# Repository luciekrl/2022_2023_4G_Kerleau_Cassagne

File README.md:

# 2022_2023_4G_Kerleau_Cassagne
Projet Capteur 4GP

## 1. Présentation du projet
### 1.1 Cadre du projet 

Ce projet de réalisation d’un capteur se basant sur une technologie low tech nous a été proposé dans le cadre du cours intitulé “du capteur au banc de test en open source hardware” que nous avons suivi lors de notre 2ème année de cycle ingénieur à l’INSA Toulouse au sein du département Génie Physique. 

Afin de récupérer les données de déformation à partir du capteur, nous avons utilisé une carte Arduino UNO. L’affichage des données se fait d’une part sur un écran OLED, et de l’autre sur un ordinateur via une interface python. Cette dernière reçoit des valeurs de déformation par une communication série établie entre l’ordinateur et la Arduino. De plus, un encodeur rotatoire permet de sélectionner les données que l’on souhaite afficher sur l’écran OLED (courbe représentant la déformation en fonction du temps, valeur de la déformation, la résistance du capteur mesurée). Enfin, nous avons ajouté un flex sensor, permettant la comparaison des données de notre capteur graphite. 

### 1.2 Principe physique

La technologie low-tech utilisée ici consiste en des traces de crayon réalisées sur un papier. Ces dernières peuvent alors servir de jauge de détection de compression et d’extension. 

Lors de la friction entre le papier et la mine de crayon, des particules de graphite restent accrochées aux fibres du papier, organisées sous forme d’un fin réseau granulaire conducteur. Lors de la contraction ou de l’extension du capteur et donc du réseau de particules de graphite, les intéractions inter-moléculaires de contact sont modifiées. En résulte une modification de la conductivité électrique globale. C’est cette variation de conductivité et donc de résistance que nous mesurons, nous donnant par un simple calcul la valeur de la déformation. Cela offre ainsi la possibilité de réaliser des capteurs de façon rapide et avec des matériaux facilement accessibles.

### 1.3 Livrables 

#### 1.3.1 Livrables initiaux

- PCB supportant le capteur graphite, l’écran OLED, l'émetteur bluetooth, l’encodeur rotatoir, le flex sensor.
- Code Arduino 
- Banc de test
- Datasheet
- Application Android récupérant les données du capteur bluetooth 

#### 1.3.2 Rectification des livrables 

Ne disposant pas d’appareil Android mais ayant quand même pour objectif de transmettre les données afin de réaliser une interface graphique, nous nous sommes tournés vers la réalisation d’une interface python. Cette dernière récupère les données de la Arduino via une communication série et permet d’afficher la courbe représentant la valeur de la déformation au cours du temps ainsi que la valeur de la déformation.

## 2. Matériel nécessaire

Pour utiliser le capteur graphite, sont nécessaires : 
Une arduino 
Un capteur grpaphite
2 pinces crocodile 
(matériel AOP) 
Logiciel : Arduino, Python 

## 3. Arduino 

Pour traiter l’information nous utilisation un microcontrôlleur Arduino UNO

### 3.1 Librairies 

Nous nous sommes servis de différentes librairies telles que les librairies de l’OLED et de l’encodeur rotatoire

### 3.2 Code 

Le code complet est disponible ici. Il gère le calibrage du capteur, l’affichage de différentes données sur l’écran OLED, la gestion de choix sur l’OLED à l’aide d’un encodeur rotatoire et enfin un envoi des données en série pour les récupérer via Python

## 4.Python

### 4.1 Librairies 

_exemples :_
* [Materialize.css](http://materializecss.com) - Framework CSS (front-end)
* [Atom](https://atom.io/) - Editeur de textes
* 

Nous nous sommes servis de différentes librairies telles que les librairies de l’OLED et de l’encodeur rotatoire

### 4.2 Code 

## 5. KiCad

Nous avons utilisé le logiciel KiCad afin de pouvoir réaliser notre PCB, pour cela nous avons dans un premier temps fait la schématique de notre montage, puis nous avons défini les empreintes de nos différents composants pour ensuite pouvoir les disposer de façon optimale sur notre PCB

### 5.1 Schématique 
### 5.2 empreintes
### 5.3 Composants

## 6. Shield 
### 6.1 PCB
### 6.2 Perçage et soudure

## 7. Simu Spice 

## 8. Tests
### 8.1 Objectifs
### 8.2 banc de test
### 8.3 résultats 
### 8.4 analyse 
### 8.5 amélioration

# 9. Datasheet

# 10. Contacts & remerciements

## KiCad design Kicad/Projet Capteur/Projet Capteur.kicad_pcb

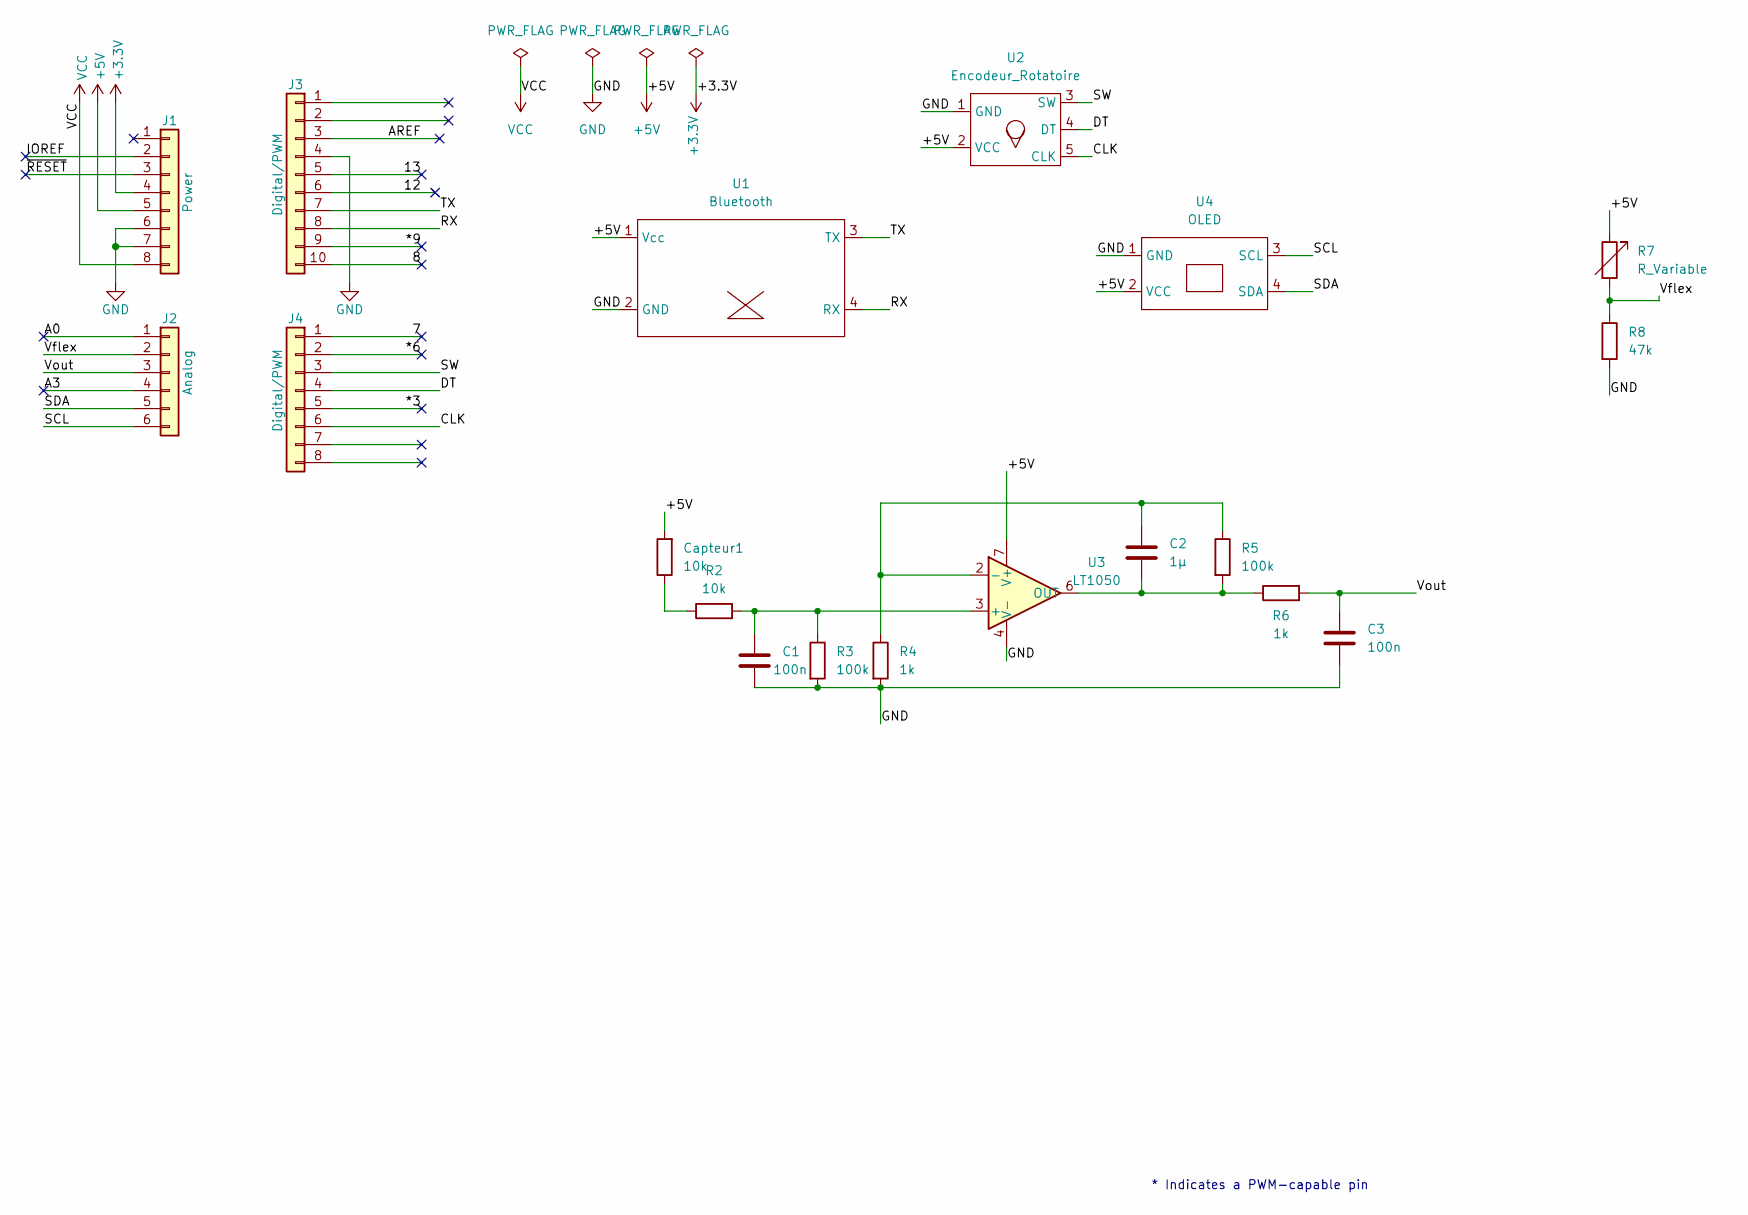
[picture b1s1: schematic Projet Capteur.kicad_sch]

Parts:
C1, C3: 100n; C_Axial_L5.1mm_D3.1mm_P10.00mm_Horizontal
C2: 1µ; C_Rect_L7.0mm_W4.5mm_P5.00mm
Capteur1: 10k; R_Axial_DIN0207_L6.3mm_D2.5mm_P10.16mm_Horizontal
J1: Power; PinSocket_1x08_P2.54mm_Vertical
J2: Analog; PinSocket_1x06_P2.54mm_Vertical
J3: Digital/PWM; PinSocket_1x10_P2.54mm_Vertical
J4: Digital/PWM; PinSocket_1x08_P2.54mm_Vertical
R2: 10k; R_Axial_DIN0207_L6.3mm_D2.5mm_P10.16mm_Horizontal
R3, R5: 100k; R_Axial_DIN0207_L6.3mm_D2.5mm_P10.16mm_Horizontal
R4, R6: 1k; R_Axial_DIN0207_L6.3mm_D2.5mm_P10.16mm_Horizontal
R7: R_Variable; R_Axial_DIN0207_L6.3mm_D2.5mm_P10.16mm_Horizontal
R8: 47k; R_Axial_DIN0207_L6.3mm_D2.5mm_P10.16mm_Horizontal
U1: Bluetooth; Bluetooth_Empreinte
U2: Encodeur_Rotatoire; Encodeur_Empreinte
U3: LT1050; DIP-8_W7.62mm_LongPads
U4: OLED; OLED_Empreinte

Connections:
+3V3: J1.4
+5V: Capteur1.2, J1.5, R7.1, U1.1 (Vcc), U2.2 (VCC), U3.7 (V+), U4.2 (VCC)
/7: J4.1
/8: J3.10
/12: J3.6
/13: J3.5
/*3: J4.5
/*6: J4.2
/*9: J3.9
/A0: J2.1
/A3: J2.4
/AREF: J3.3
/CLK: J4.6, U2.5 (CLK)
/DT: J4.4, U2.4 (DT)
/IOREF: J1.2
/RX: J3.8, U1.4 (RX)
/SCL: J2.6, U4.3 (SCL)
/SDA: J2.5, U4.4 (SDA)
/SW: J4.3, U2.3 (SW)
/TX: J3.7, U1.3 (TX)
/Vflex: J2.2, R7.2, R8.1
/Vout: C3.1, J2.3, R6.2
/~RESET: J1.3
GND: C1.2, C3.2, J1.6, J1.7, J3.4, R3.2, R4.2, R8.2, U1.2 (GND), U2.1 (GND), U3.4 (V-), U4.1 (GND)
unnamed: C1.1, R2.2, R3.1, U3.3 (+)
unnamed: C2.1, R5.2, R6.1, U3.6 (OUT)
unnamed: C2.2, R4.1, R5.1, U3.2 (-)
unnamed: Capteur1.1, R2.1
VCC: J1.8

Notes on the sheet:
* Indicates a PWM-capable pin

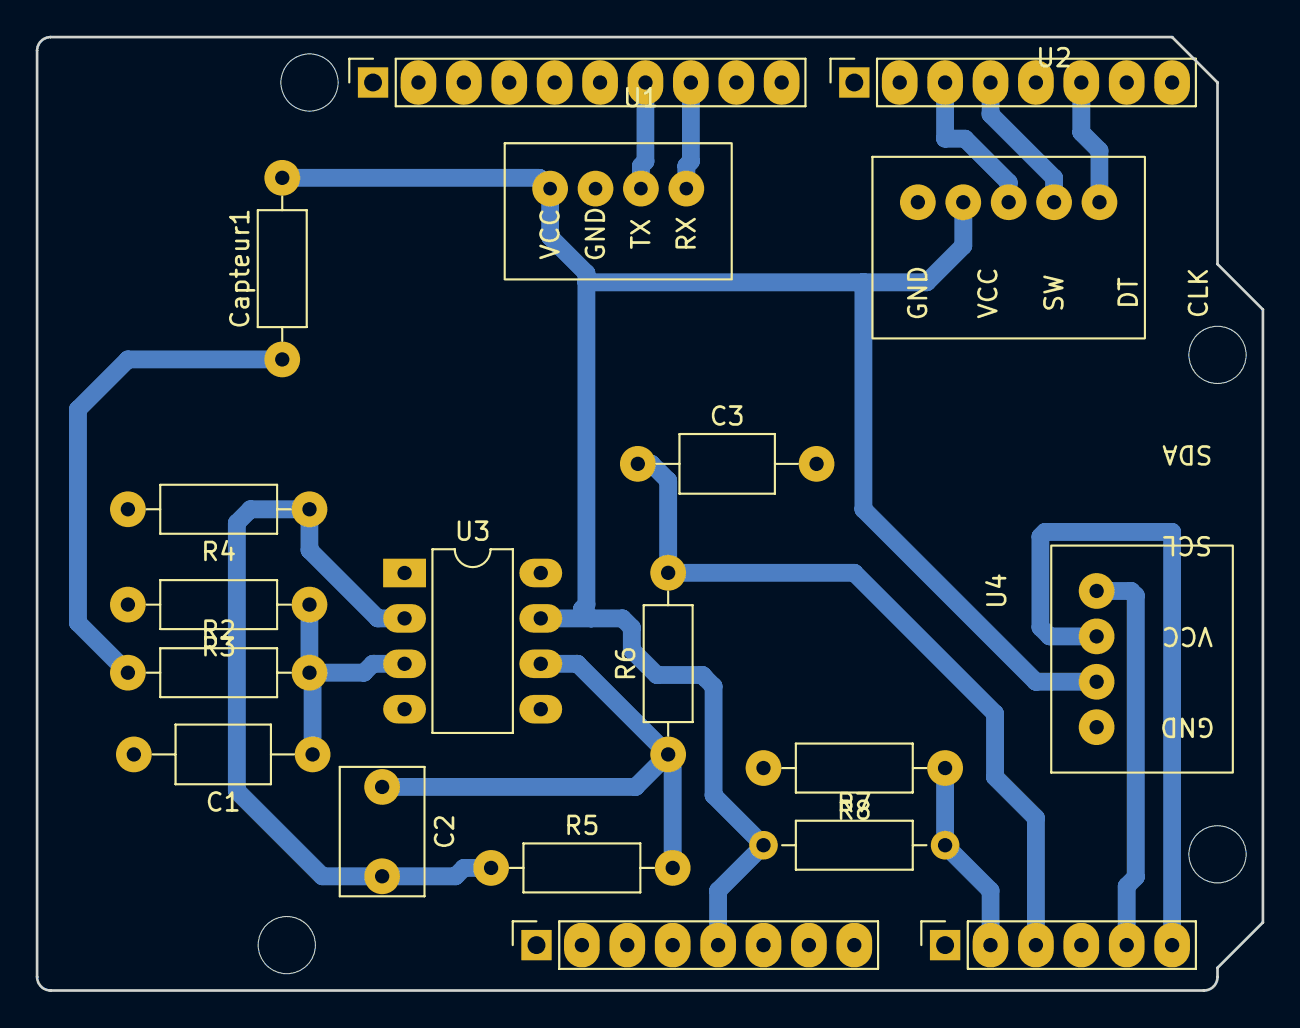
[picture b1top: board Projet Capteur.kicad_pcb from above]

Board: 2 copper layers, 68.6 x 53.3 mm, 23 parts (0 on the bottom side), 15 nets.

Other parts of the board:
MH1, MH2, MH3, MH4: MountingHole_3.2mm

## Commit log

2023-05-15 Ajout du dossier Kicad
